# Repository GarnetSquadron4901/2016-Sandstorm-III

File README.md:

#2016 Robot Code - Sandstorm III - FIRST Robotics Team 4901 - Garnet Squadron

## Languages
- Robot - LabVIEW
- Dashboard - LabVIEW
- Vision Processing on Raspberry Pi
	- LED Control - Python
	- Vision Processing - Java using GRIP

## Features
- 8 drive modes
	- Arcade
	- Split Axis Arcade
	- Tank
	- Vision
	- Encoder Distance
	- Braked
	- Ultrasonic Distance
	- IMU Yaw Feedback
- Arm Control
	- PID
	- Preset Buttons
	- Manual arm control with closed-loop feedback from potentiometer
	- Automatic locking/unlocking with pneumatic cylinders
	- Automatic arm raising when driving faster than a preset speed
- Parameters - Most robot constants are parameterized to allow run-time changes to parameters such as arm angles, voltage to angle conversion, etc. 
- [Custom operator interface](https://github.com/GarnetSquardon4901/Operator-Interface-Control-Board)

## Checkout Process
To check out the Sandstorm III repository, simply download the [update.bat](https://github.com/GarnetSquardon4901/2016-Sand-Storm-III/raw/master/update.bat) and run it.

You'll need to install TortoiseSVN v1.8.x from [SourceForge](https://sourceforge.net/projects/tortoisesvn/files/). Newer versions (such as v1.9) don't work with the LabVIEW Plugin TSVN. Be sure to install the option for Command line tools.

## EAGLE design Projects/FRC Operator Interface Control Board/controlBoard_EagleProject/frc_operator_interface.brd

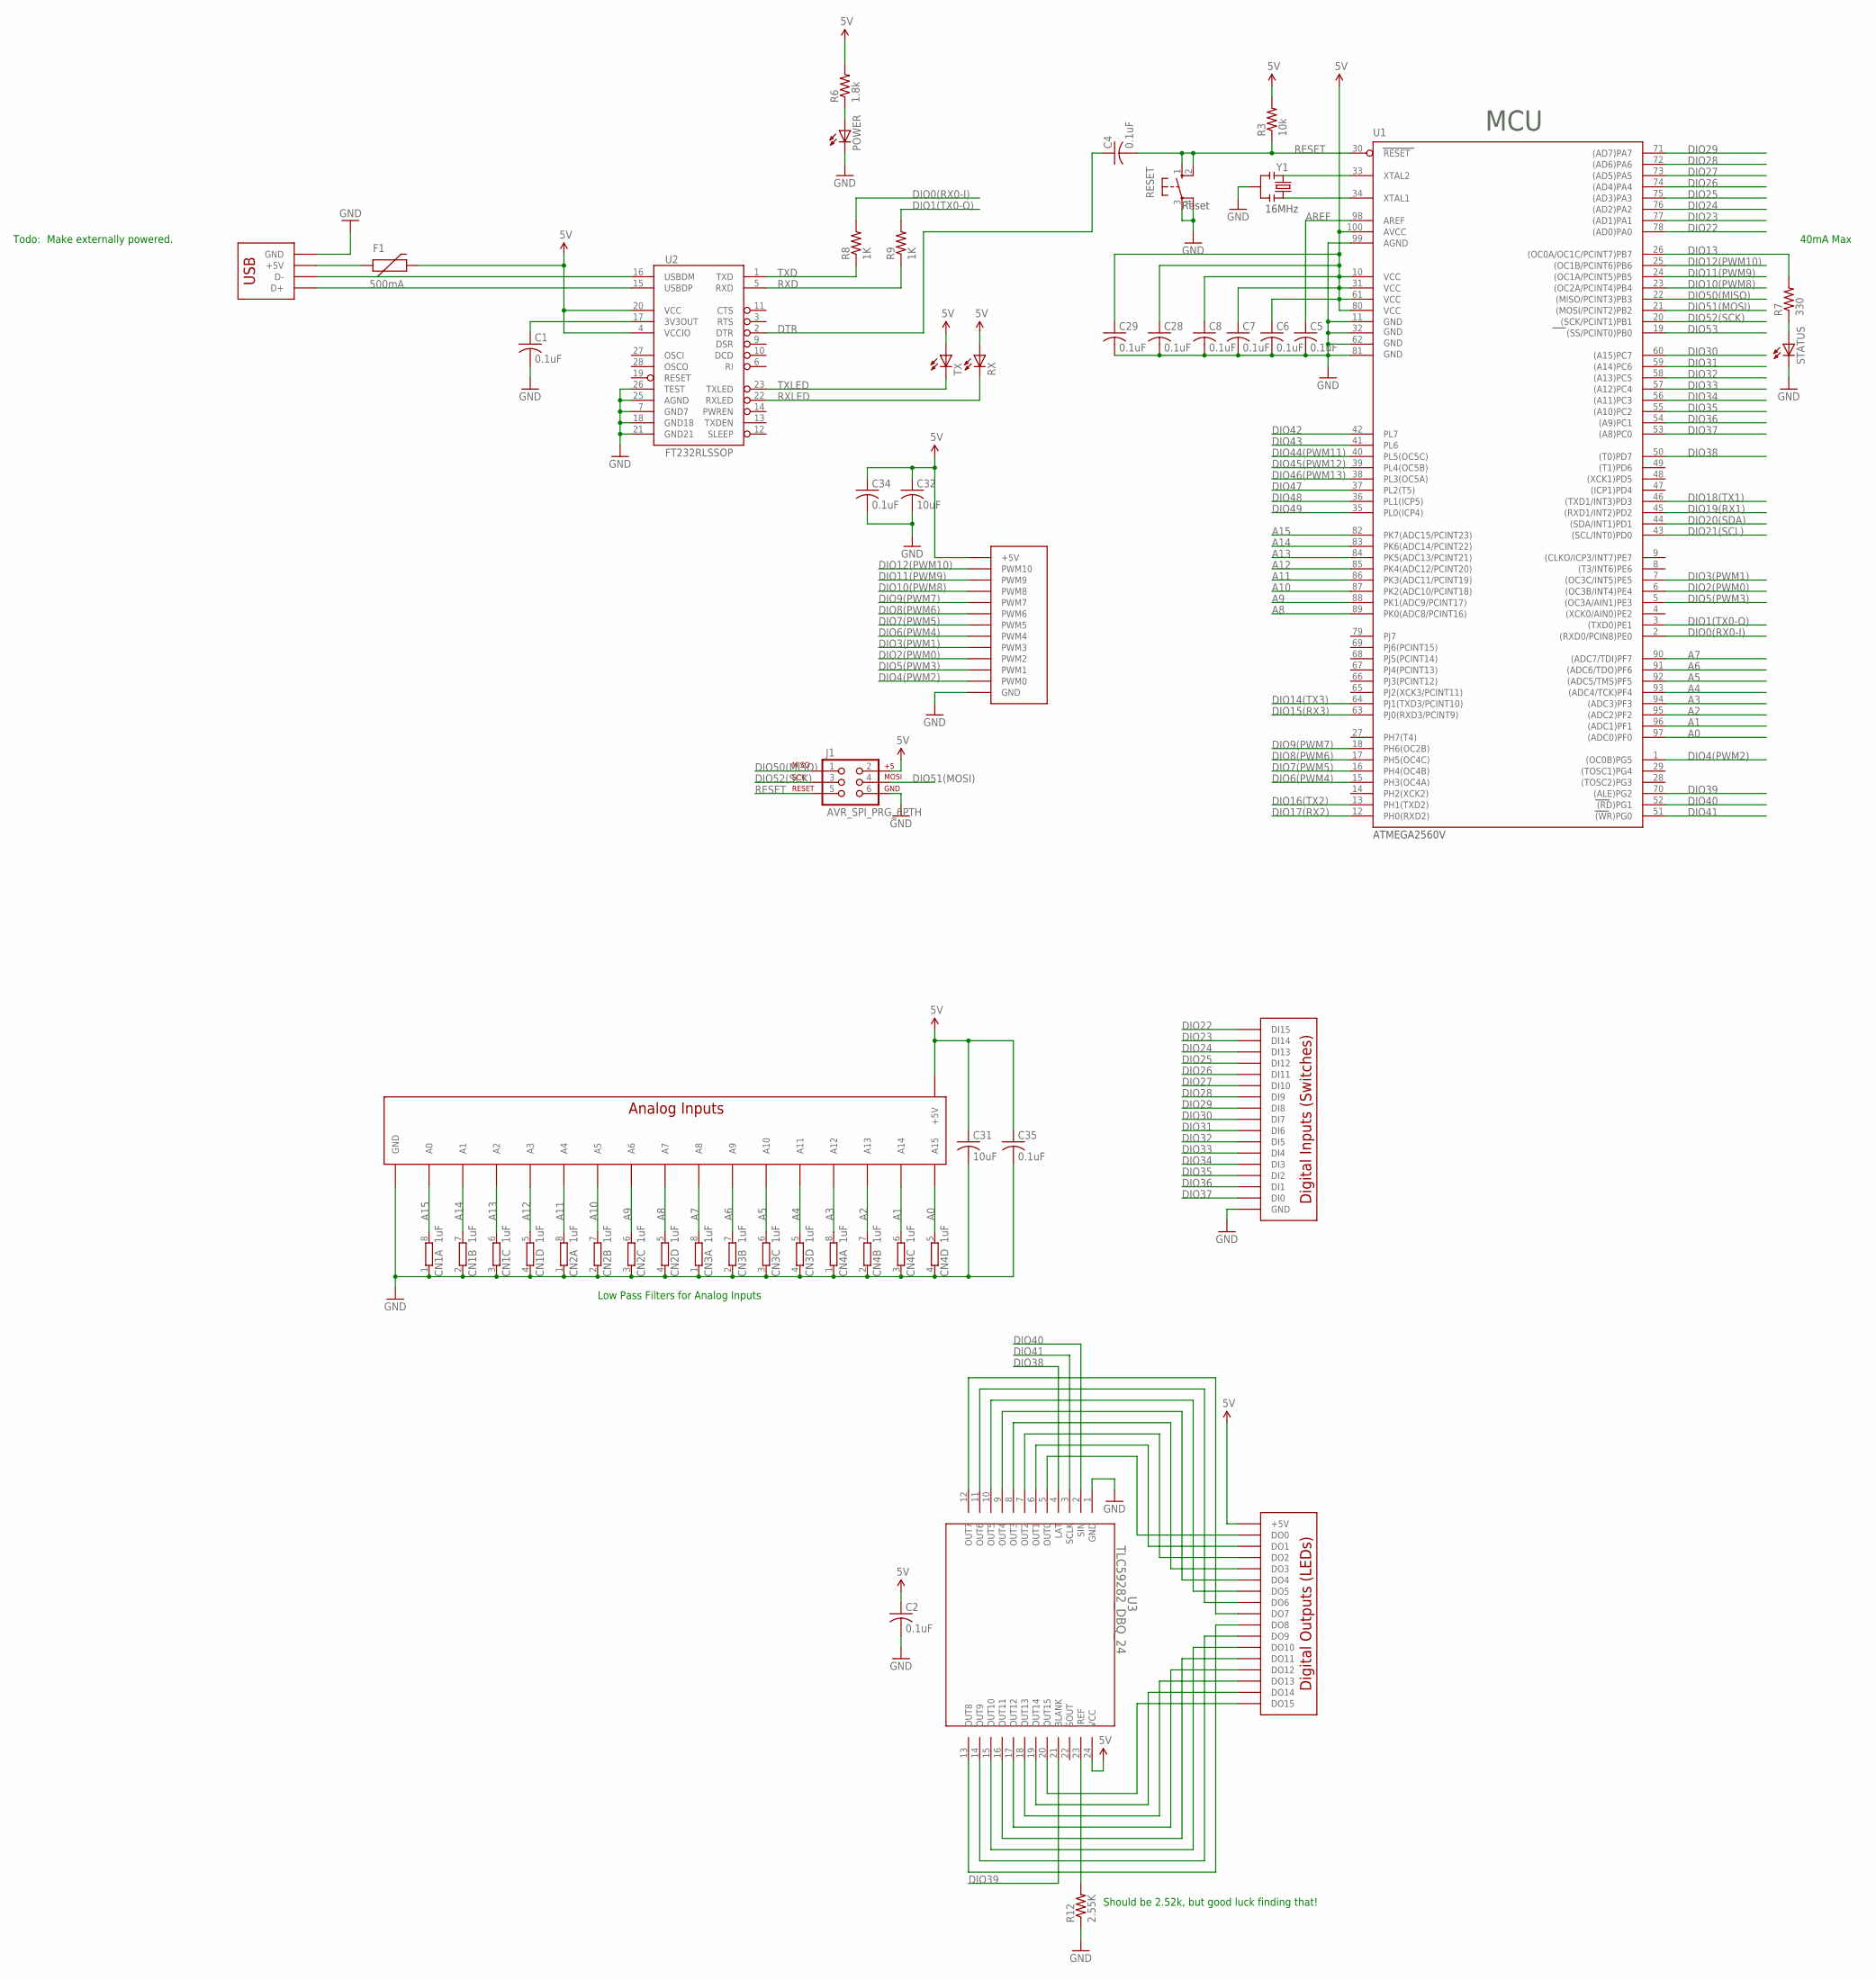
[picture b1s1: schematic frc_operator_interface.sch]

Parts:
C1, C2, C4, C5, C6, C7, C8, C28, C29, C34, C35: 0.1uF; C1206
C31, C32: 10uF; C1206
CN1, CN2, CN3, CN4: 1uF; EXB38V
F1: 500mA; PTC-1206
J1: AVR_SPI_PRG_6PTH; 2X3
J2: ANALOGHEADER
J3: DIGITALIN
J4: DIGITALOUTPUTS; DIGITALOUT
J5: PWMHEADER
J6: UE27BC54130-USB
POWER: LED3MM
R3: 10k; M1206
R6: 1.8k; M1206
R7: 330; M1206
R8, R9: 1K; M1206
R12: 2.55K; M1206
RESET: 10-XX; B3F-10XX
RX: LED3MM
STATUS: LED3MM
TX: LED3MM
U1: ATMEGA2560AU; TQFP100
U2: FT232RLSSOP; SSOP28DB
U3: TLC59282_DBQ_24; DBQ24
Y1: RESONATORSMD; RESONATOR-SMD

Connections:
5V: C2.1, C6.1, C7.1, C8.1, C28.1, C29.1, C31.1, C32.1, C34.1, C35.1, F1.2, J1.2, J2.+5V@0 (+5V), J2.+5V@1 (+5V), J2.+5V@2 (+5V), J2.+5V@3 (+5V), J2.+5V@4 (+5V), J2.+5V@5 (+5V), J2.+5V@6 (+5V), J2.+5V@7 (+5V), J2.+5V@8 (+5V), J2.+5V@9 (+5V), J2.+5V@10 (+5V), J2.+5V@11 (+5V), J2.+5V@12 (+5V), J2.+5V@13 (+5V), J2.+5V@14 (+5V), J2.+5V@15 (+5V), J4.+5V@0 (+5V), J4.+5V@1 (+5V), J4.+5V@2 (+5V), J4.+5V@3 (+5V), J4.+5V@4 (+5V), J4.+5V@5 (+5V), J4.+5V@6 (+5V), J4.+5V@7 (+5V), J4.+5V@8 (+5V), J4.+5V@9 (+5V), J4.+5V@10 (+5V), J4.+5V@11 (+5V), J4.+5V@12 (+5V), J4.+5V@13 (+5V), J4.+5V@14 (+5V), J4.+5V@15 (+5V), J5.+5V@3 (+5V), J5.+5V@4 (+5V), J5.+5V@5 (+5V), J5.+5V@6 (+5V), J5.+5V@7 (+5V), J5.+5V@8 (+5V), J5.+5V@9 (+5V), J5.+5V@10 (+5V), J5.+5V@11 (+5V), J5.+5V@12 (+5V), J5.+5V@13 (+5V), R3.2, R6.2, RX.A, TX.A, U1.10 (VCC), U1.31 (VCC1), U1.61 (VCC2), U1.80 (VCC3), U1.100 (AVCC), U2.4 (VCCIO), U2.20 (VCC), U3.24 (VCC)
A0: CN4.5 (2), J2.15 (A15), U1.97 ((ADC0)PF0)
A1: CN4.6 (2), J2.14 (A14), U1.96 ((ADC1)PF1)
A2: CN4.7 (2), J2.13 (A13), U1.95 ((ADC2)PF2)
A3: CN4.8 (2), J2.12 (A12), U1.94 ((ADC3)PF3)
A4: CN3.5 (2), J2.11 (A11), U1.93 ((ADC4/TCK)PF4)
A5: CN3.6 (2), J2.10 (A10), U1.92 ((ADC5/TMS)PF5)
A6: CN3.7 (2), J2.9 (A9), U1.91 ((ADC6/TDO)PF6)
A7: CN3.8 (2), J2.8 (A8), U1.90 ((ADC7/TDI)PF7)
A8: CN2.5 (2), J2.7 (A7), U1.89 (PK0(ADC8/PCINT16))
A9: CN2.6 (2), J2.6 (A6), U1.88 (PK1(ADC9/PCINT17))
A10: CN2.7 (2), J2.5 (A5), U1.87 (PK2(ADC10/PCINT18))
A11: CN2.8 (2), J2.4 (A4), U1.86 (PK3(ADC11/PCINT19))
A12: CN1.5 (2), J2.3 (A3), U1.85 (PK4(ADC12/PCINT20))
A13: CN1.6 (2), J2.2 (A2), U1.84 (PK5(ADC13/PCINT21))
A14: CN1.7 (2), J2.1 (A1), U1.83 (PK6(ADC14/PCINT22))
A15: CN1.8 (2), J2.0 (A0), U1.82 (PK7(ADC15/PCINT23))
AREF: C5.1, U1.98 (AREF)
DIO0(RX0-I): R8.2, U1.2 ((RXD0/PCIN8)PE0)
DIO1(TX0-O): R9.2, U1.3 ((TXD0)PE1)
DIO2(PWM0): J5.2 (PWM2), U1.6 ((OC3B/INT4)PE4)
DIO3(PWM1): J5.3 (PWM3), U1.7 ((OC3C/INT5)PE5)
DIO4(PWM2): J5.0 (PWM0), U1.1 ((OC0B)PG5)
DIO5(PWM3): J5.1 (PWM1), U1.5 ((OC3A/AIN1)PE3)
DIO6(PWM4): J5.4 (PWM4), U1.15 (PH3(OC4A))
DIO7(PWM5): J5.5 (PWM5), U1.16 (PH4(OC4B))
DIO8(PWM6): J5.6 (PWM6), U1.17 (PH5(OC4C))
DIO9(PWM7): J5.7 (PWM7), U1.18 (PH6(OC2B))
DIO10(PWM8): J5.8 (PWM8), U1.23 ((OC2A/PCINT4)PB4)
DIO11(PWM9): J5.9 (PWM9), U1.24 ((OC1A/PCINT5)PB5)
DIO12(PWM10): J5.10 (PWM10), U1.25 ((OC1B/PCINT6)PB6)
DIO13: R7.2, U1.26 ((OC0A/OC1C/PCINT7)PB7)
DIO14(TX3): U1.64 (PJ1(TXD3/PCINT10))
DIO15(RX3): U1.63 (PJ0(RXD3/PCINT9))
DIO16(TX2): U1.13 (PH1(TXD2))
DIO17(RX2): U1.12 (PH0(RXD2))
DIO18(TX1): U1.46 ((TXD1/INT3)PD3)
DIO19(RX1): U1.45 ((RXD1/INT2)PD2)
DIO20(SDA): U1.44 ((SDA/INT1)PD1)
DIO21(SCL): U1.43 ((SCL/INT0)PD0)
DIO22: J3.DI15, U1.78 ((AD0)PA0)
DIO23: J3.DI14, U1.77 ((AD1)PA1)
DIO24: J3.DI13, U1.76 ((AD2)PA2)
DIO25: J3.DI12, U1.75 ((AD3)PA3)
DIO26: J3.DI11, U1.74 ((AD4)PA4)
DIO27: J3.DI10, U1.73 ((AD5)PA5)
DIO28: J3.DI9, U1.72 ((AD6)PA6)
DIO29: J3.DI8, U1.71 ((AD7)PA7)
DIO30: J3.DI7, U1.60 ((A15)PC7)
DIO31: J3.DI6, U1.59 ((A14)PC6)
DIO32: J3.DI5, U1.58 ((A13)PC5)
DIO33: J3.DI4, U1.57 ((A12)PC4)
DIO34: J3.DI3, U1.56 ((A11)PC3)
DIO35: J3.DI2, U1.55 ((A10)PC2)
DIO36: J3.DI1, U1.54 ((A9)PC1)
DIO37: J3.DI0, U1.53 ((A8)PC0)
DIO38: U1.50 ((T0)PD7), U3.4 (LAT)
DIO39: U1.70 ((ALE)PG2), U3.21 (BLANK)
DIO40: U1.52 ((RD)PG1), U3.2 (SIN)
DIO41: U1.51 ((WR)PG0), U3.3 (SCLK)
DIO42: U1.42 (PL7)
DIO43: U1.41 (PL6)
DIO44(PWM11): U1.40 (PL5(OC5C))
DIO45(PWM12): U1.39 (PL4(OC5B))
DIO46(PWM13): U1.38 (PL3(OC5A))
DIO47: U1.37 (PL2(T5))
DIO48: U1.36 (PL1(ICP5))
DIO49: U1.35 (PL0(ICP4))
DIO50(MISO): J1.1, U1.22 ((MISO/PCINT3)PB3)
DIO51(MOSI): J1.4, U1.21 ((MOSI/PCINT2)PB2)
DIO52(SCK): J1.3, U1.20 ((SCK/PCINT1)PB1)
DIO53: U1.19 ((SS/PCINT0)PB0)
DTR: C4.1, U2.2 (DTR)
GND: C1.2, C2.2, C5.2, C6.2, C7.2, C8.2, C28.2, C29.2, C31.2, C32.2, C34.2, C35.2, CN1.1, CN1.2 (1), CN1.3 (1), CN1.4 (1), CN2.1, CN2.2 (1), CN2.3 (1), CN2.4 (1), CN3.1, CN3.2 (1), CN3.3 (1), CN3.4 (1), CN4.1, CN4.2 (1), CN4.3 (1), CN4.4 (1), J1.6, J2.GND@0 (GND), J2.GND@1 (GND), J2.GND@2 (GND), J2.GND@3 (GND), J2.GND@4 (GND), J2.GND@5 (GND), J2.GND@6 (GND), J2.GND@7 (GND), J2.GND@8 (GND), J2.GND@9 (GND), J2.GND@10 (GND), J2.GND@11 (GND), J2.GND@12 (GND), J2.GND@13 (GND), J2.GND@14 (GND), J2.GND@15 (GND), J3.GND@0 (GND), J3.GND@1 (GND), J3.GND@2 (GND), J3.GND@3 (GND), J3.GND@4 (GND), J3.GND@5 (GND), J3.GND@6 (GND), J3.GND@7 (GND), J3.GND@8 (GND), J3.GND@9 (GND), J3.GND@10 (GND), J3.GND@11 (GND), J3.GND@12 (GND), J3.GND@13 (GND), J3.GND@14 (GND), J3.GND@15 (GND), J5.GND@3 (GND), J5.GND@4 (GND), J5.GND@5 (GND), J5.GND@6 (GND), J5.GND@7 (GND), J5.GND@8 (GND), J5.GND@9 (GND), J5.GND@10 (GND), J5.GND@11 (GND), J5.GND@12 (GND), J5.GND@13 (GND), J6.GND@0 (GND), J6.GND@1 (GND), J6.GND@2 (GND), POWER.K (C), R12.1, RESET.3, RESET.4 (P1), STATUS.K (C), U1.11 (GND), U1.32 (GND1), U1.62 (GND2), U1.81 (GND3), U1.99 (AGND), U2.7 (GND7), U2.18 (GND18), U2.21 (GND21), U2.25 (AGND), U2.26 (TEST), U3.1 (GND), Y1.2
unnamed: POWER.A, R6.1
unnamed: R7.1, STATUS.A
unnamed: F1.1, J6.+5V
unnamed: C1.1, U2.17 (3V3OUT)
unnamed: J4.DO1, U3.6 (OUT1)
unnamed: J4.DO2, U3.7 (OUT2)
unnamed: J4.DO0, U3.5 (OUT0)
unnamed: J4.DO3, U3.8 (OUT3)
unnamed: J4.DO4, U3.9 (OUT4)
unnamed: J4.DO5, U3.10 (OUT5)
unnamed: J4.DO6, U3.11 (OUT6)
unnamed: J4.DO7, U3.12 (OUT7)
unnamed: J4.DO15, U3.20 (OUT15)
unnamed: J4.DO14, U3.19 (OUT14)
unnamed: J4.DO13, U3.18 (OUT13)
unnamed: J4.DO12, U3.17 (OUT12)
unnamed: J4.DO11, U3.16 (OUT11)
unnamed: J4.DO10, U3.15 (OUT10)
unnamed: J4.DO9, U3.14 (OUT9)
unnamed: J4.DO8, U3.13 (OUT8)
unnamed: R12.2, U3.23 (IREF)
unnamed: U1.33 (XTAL2), Y1.1
unnamed: U1.34 (XTAL1), Y1.3
RESET: C4.2, J1.5, R3.1, RESET.1 (S), RESET.2 (S1), U1.30 (RESET)
RXD: R9.1, U2.5 (RXD)
RXLED: RX.K (C), U2.22 (RXLED)
TXD: R8.1, U2.1 (TXD)
TXLED: TX.K (C), U2.23 (TXLED)
USB_D_N: J6.-DATA (D-), U2.16 (USBDM)
USB_D_P: J6.+DATA (D+), U2.15 (USBDP)

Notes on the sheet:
MCU
16MHz
ATMEGA2560V
Reset
Low Pass Filters for Analog Inputs
40mA Max
Todo:
Make externally powered.
Should be 2.52k, but good luck finding that!

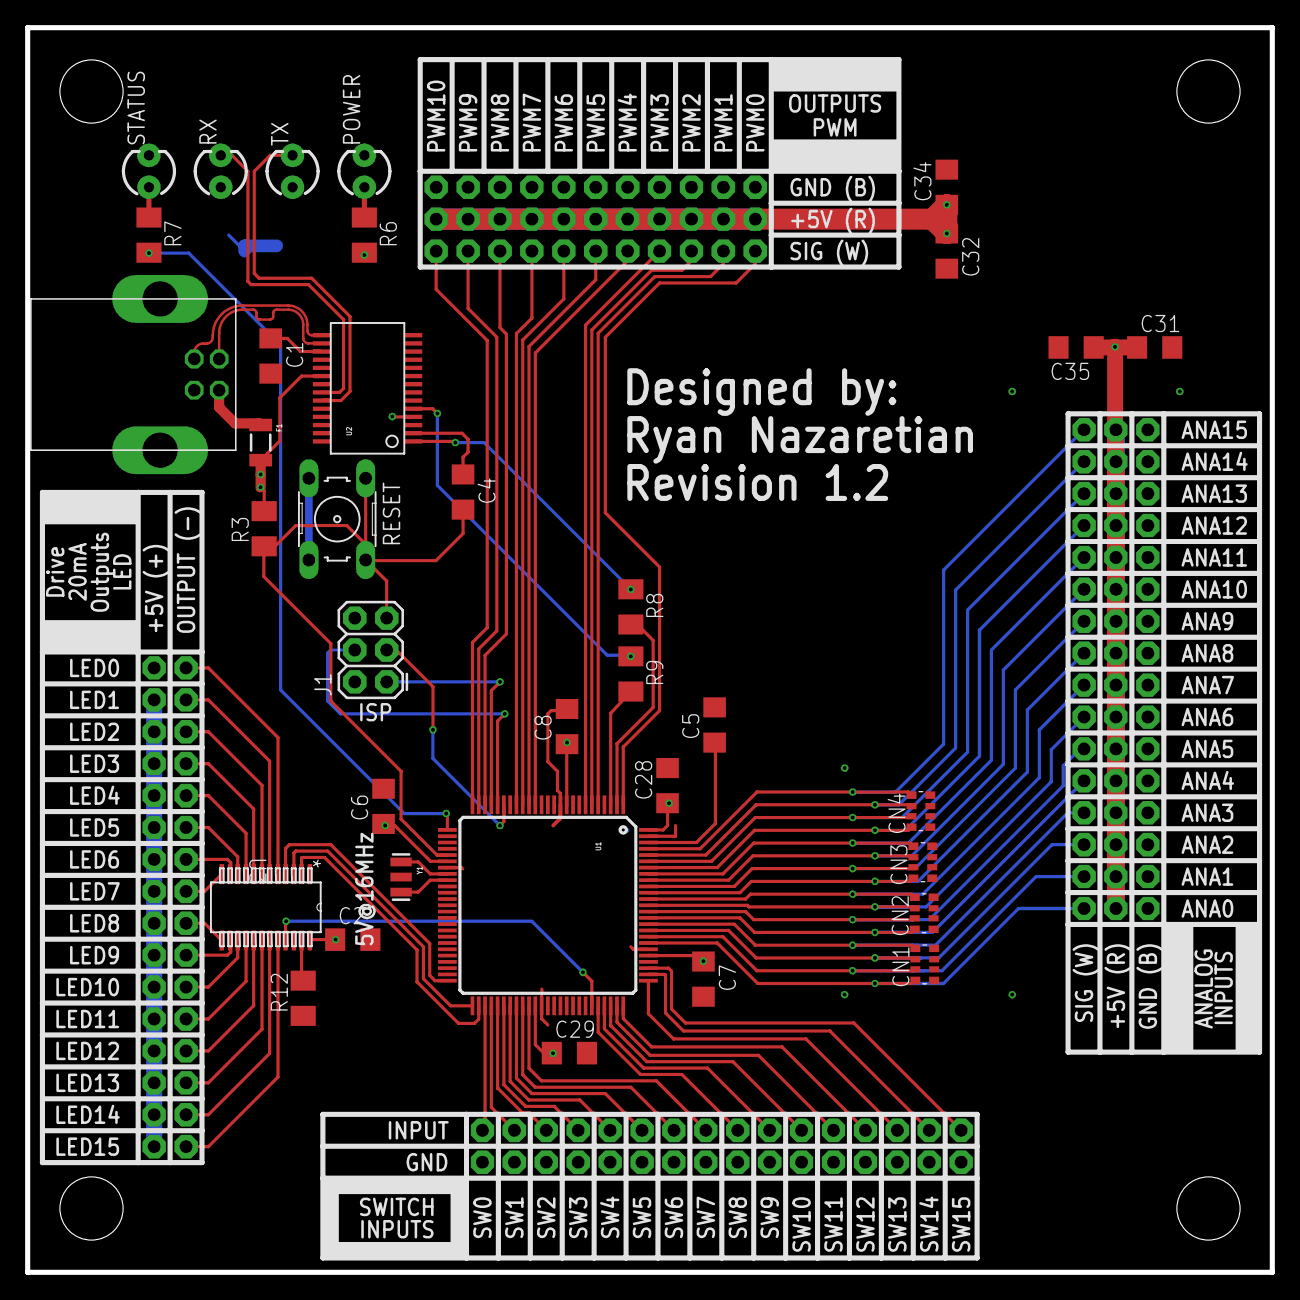
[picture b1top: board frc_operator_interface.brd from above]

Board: 2 copper layers, 99.1 x 99.1 mm, 39 parts (0 on the bottom side), 87 nets.

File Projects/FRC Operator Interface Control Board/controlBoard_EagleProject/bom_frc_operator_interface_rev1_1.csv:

Qty,Value,Device,Package,Parts,Description,DATASHEETURL,DESCRIPTION,FAMILY_NAME,DIGIKEY_PART_NUMBER,INDUSTRY_STD_PKG_TYPE,MANUFACTURER,MANUFACTURER_PART_NUMBER,MF,MPN,OC_FARNELL,OC_NEWARK,PACKAGE_DESIGNATOR,PIN_COUNT,PROD_ID,VENDOR
1,,10-XX,B3F-10XX,RESET,OMRON SWITCH,,Reset Switch,,SW400-ND,,,,,B3F-1000,176432,36M3542,,,,
4,,LED3MM,LED3MM,"POWER, RX, STATUS, TX",LEDs,,,,,,,,,,,,,,,
11,0.1uF,C-USC1206,C1206,"C1, C2, C4, C5, C6, C7, C8, C28, C29, C34, C35","CAPACITOR, American symbol",,,,,,,,,,,,,,,
1,10k,R-US_M1206,M1206,R3,"RESISTOR, American symbol",,,,,,,,,,,,,,,
2,10uF,C-USC1206,C1206,"C31, C32","CAPACITOR, American symbol",,,,,,,,,,,,,,,
1,170,R-US_M1206,M1206,R6,"RESISTOR, American symbol",,,,,,,,,,,,,,,
2,1K,R-US_M1206,M1206,"R8, R9","RESISTOR, American symbol",,,,,,,,,,,,,,,
4,1uF,4R-NEXB38V,EXB38V,"CN1, CN2, CN3, CN4",Array Chip Resistor,,,,,,,,,,unknown,unknown,,,,
1,2.52K,R-US_M1206,M1206,R12,"RESISTOR, American symbol",,,,,,,,,,,,,,,
1,280,R-US_M1206,M1206,R1,"RESISTOR, American symbol",,,,,,,,,,,,,,,
1,300,R-US_M1206,M1206,R7,"RESISTOR, American symbol",,,,,,,,,,,,,,,
1,315,R-US_M1206,M1206,R2,"RESISTOR, American symbol",,,,,,,,,,,,,,,
1,500mA,PTCSMD,PTC-1206,F1,Resettable Fuse PTC,,,,,,,,,,,,,,RES-11150,
1,ANALOGHEADER,ANALOGHEADER,ANALOGHEADER,U$12,,,,,,,,,,,,,,,,
1,ATMEGA2560AU,ATMEGA2560AU,TQFP100,GND,MICROCONTROLLER,,,,,,,,,,,,,,,
1,AVR_SPI_PRG_6PTH,AVR_SPI_PRG_6PTH,2X3,J1,AVR ISP 6 Pin,,,,,,,,,,,,,,,
1,DIGITALIN,DIGITALIN,DIGITALIN,U$2,,,,,,,,,,,,,,,,
1,DIGITALOUTPUTS,DIGITALOUTPUTS,DIGITALOUT,U$11,,,,,,,,,,,,,,,,
1,FT232RLSSOP,FT232RLSSOP,SSOP28DB,U4,USB UART,,,,,,,,,,,,,,,
1,PWMHEADER,PWMHEADER,PWMHEADER,U$10,,,,,,,,,,,,,,,,
1,RESONATORSMD,RESONATORSMD,RESONATOR-SMD,Y1,Resonator,,,,,,,,,,,,,,,
1,TLC59282_DBQ_24,TLC59282_DBQ_24,DBQ24,U1,,http://www.ti.com/lit/gpn/TLC59282,16-Channel Constant Current LED Driver with 4-Channel Grouped Delay,LED DRIVER,TLC59282,SSOP/QSOP,Texas Instruments,tlc59282_dbq_24,,,,,DBQ,24,,Texas Instruments
1,UE27BC54130-USB,UE27BC54130-USB,UE27BC54130-USB,U$14,,,,,,,,,,,,,,,,

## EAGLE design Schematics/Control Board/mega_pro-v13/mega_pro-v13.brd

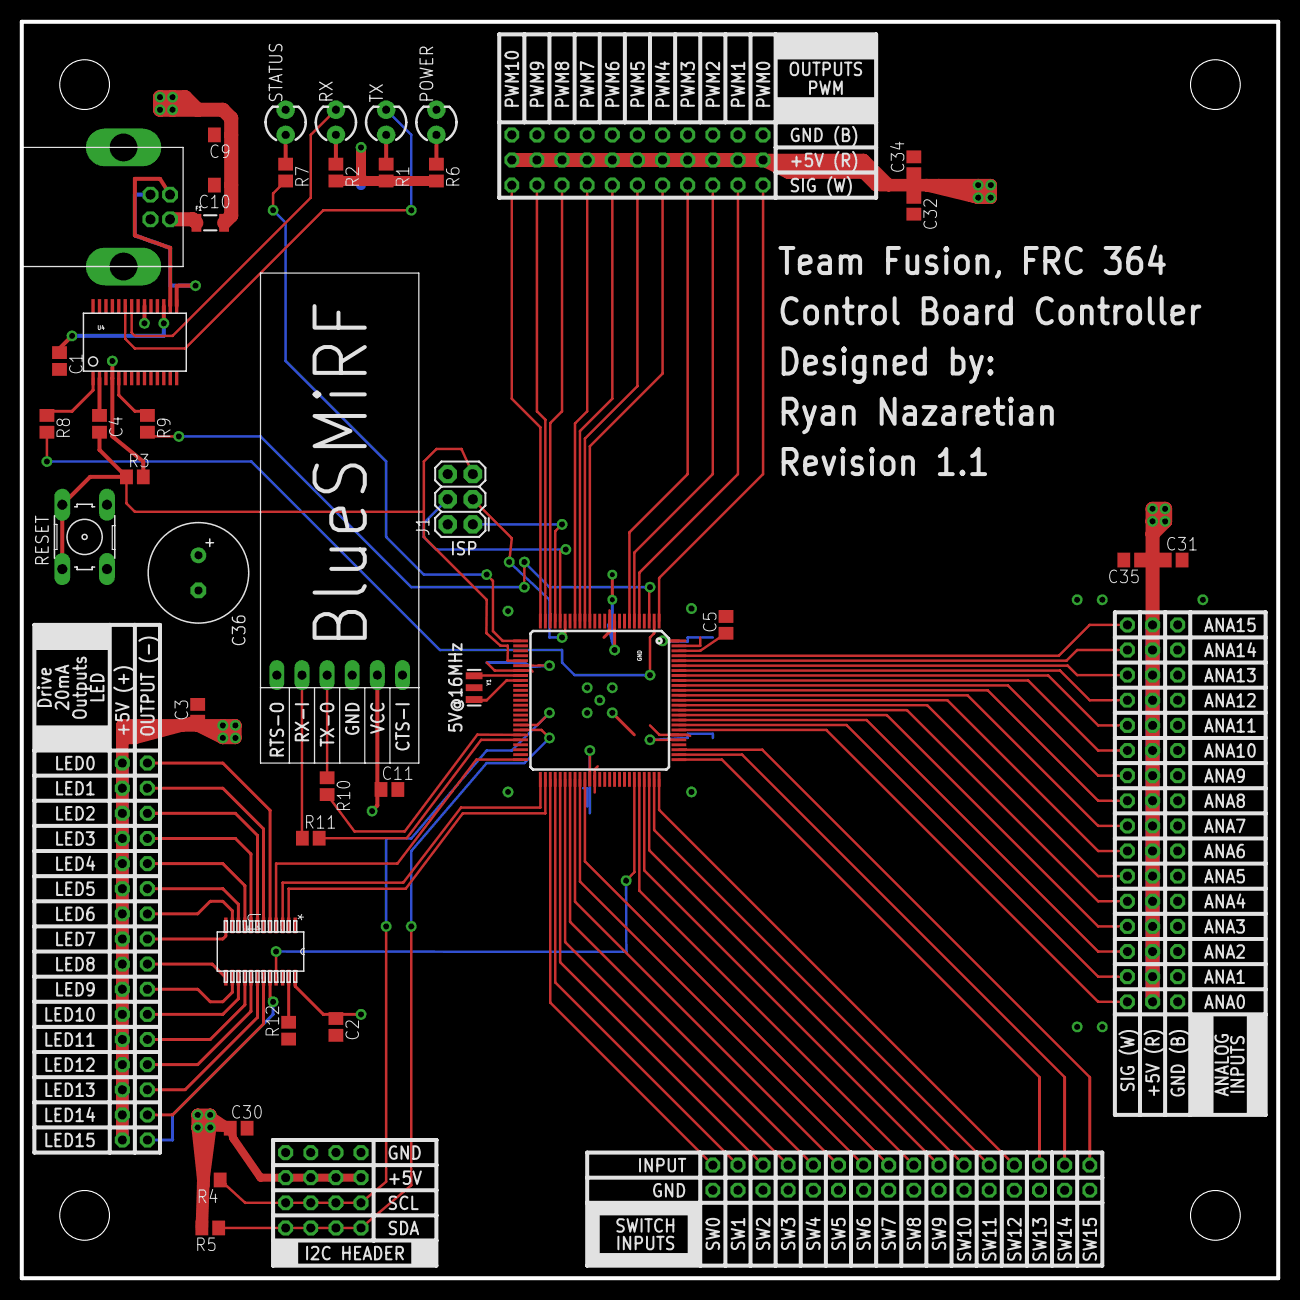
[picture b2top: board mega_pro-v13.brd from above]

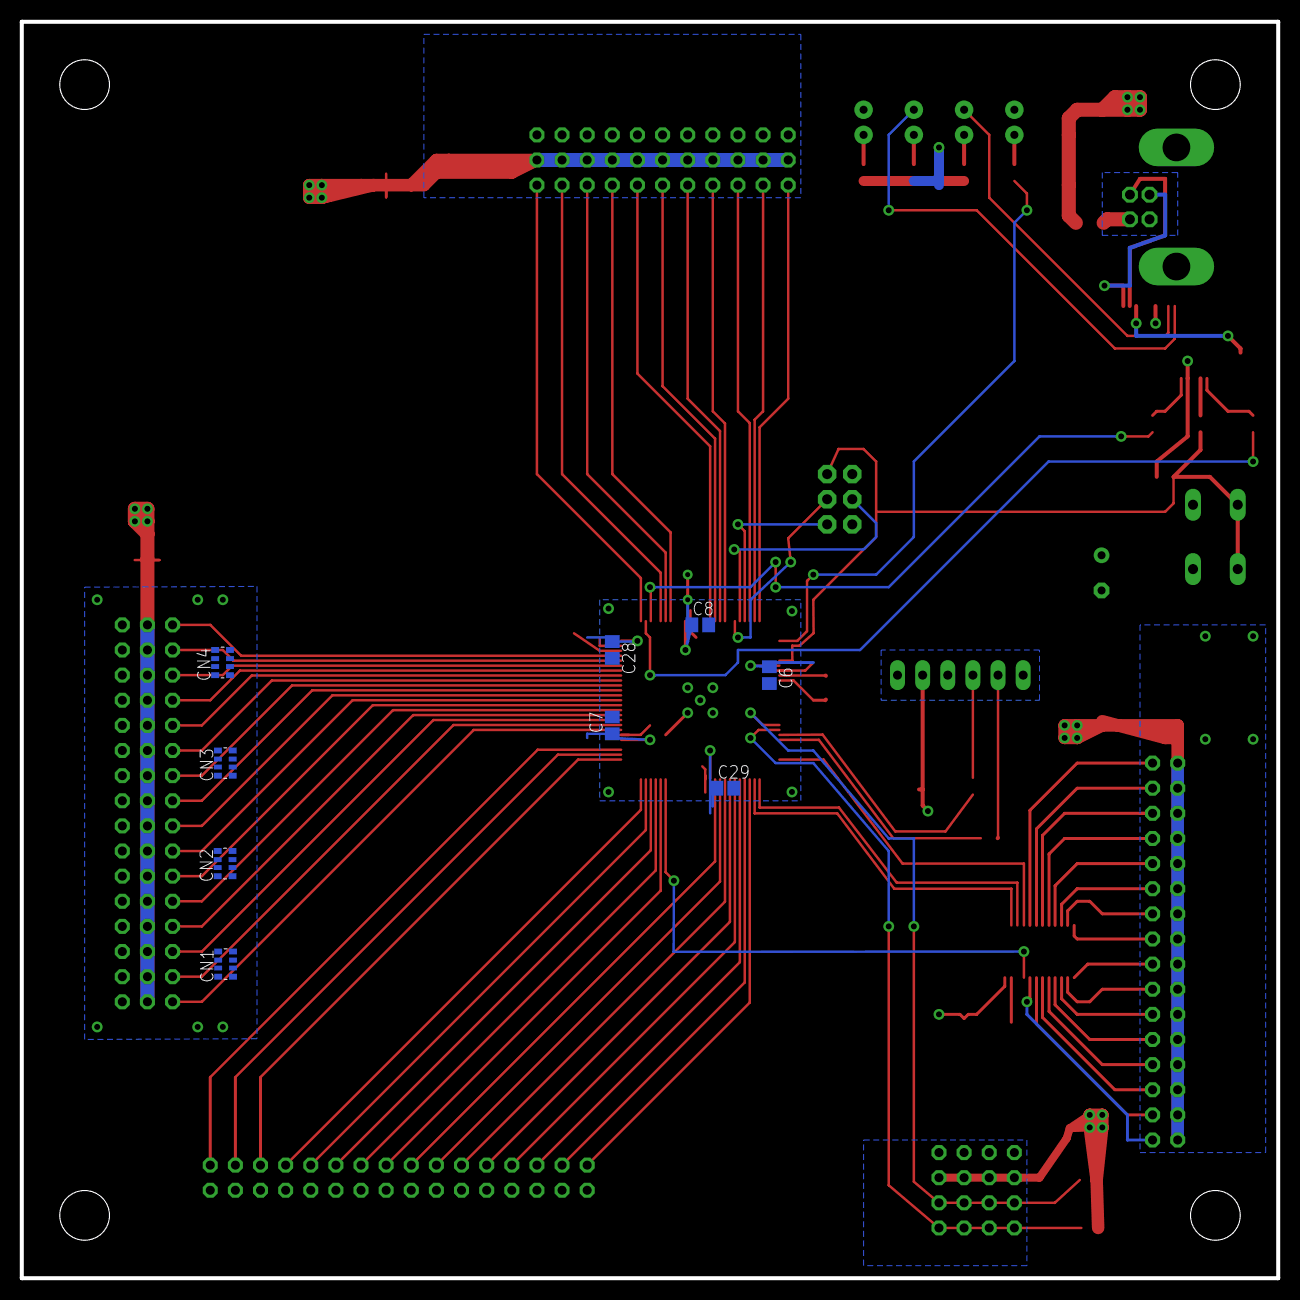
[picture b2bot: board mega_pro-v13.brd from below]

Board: 2 copper layers, 127.0 x 127.0 mm, 53 parts (9 on the bottom side), 95 nets.

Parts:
C1, C2, C4, C5, C6, C7, C8, C9, C28, C29, C34, C35: 0.1uF; C0805
C3, C10, C11, C30, C31, C32: 10uF; C0805
C36: 470uF; E3,5-10
CN1, CN2, CN3, CN4: 1uF; EXB38V
F1: 500mA; PTC-1206
GND: ATMEGA2560AU; TQFP100
J1: AVR_SPI_PRG_6PTH; 2X3
POWER: LED3MM
R1: 140; R0805
R2: 157.5; R0805
R3, R4, R5: 10k; R0805
R6: 85; R0805
R7: 150; R0805
R8, R9, R10, R11: 1K; R0805
R12: 2.52K; R0805
RESET: B3F-10XX
RX: LED3MM
STATUS: LED3MM
TX: LED3MM
U1: TLC59282_DBQ_24; DBQ24
U4: FT232RLSSOP; SSOP28DB
U$2: DIGITALIN
U$10: PWMHEADER
U$11: DIGITALOUTPUTS; DIGITALOUT
U$12: ANALOGHEADER
U$14: UE27BC54130-USB
U$15: I2CHEADER
U$19: BLUESMIRF
Y1: RESONATORSMD; RESONATOR-SMD

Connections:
5V: C2.1, C3.1, C6.1, C7.1, C8.1, C9.1, C10.1, C11.1, C28.1, C29.1, C30.1, C31.1, C32.1, C34.1, C35.1, C36.+, F1.2, GND.10, GND.31, GND.61, GND.80, GND.100, J1.2, R1.2, R2.2, R3.2, R4.2, R5.2, R6.2, U1.24, U4.4, U4.20, U$10.+5V@3, U$10.+5V@4, U$10.+5V@5, U$10.+5V@6, U$10.+5V@7, U$10.+5V@8, U$10.+5V@9, U$10.+5V@10, U$10.+5V@11, U$10.+5V@12, U$10.+5V@13, U$11.+5V@0, U$11.+5V@1, U$11.+5V@2, U$11.+5V@3, U$11.+5V@4, U$11.+5V@5, U$11.+5V@6, U$11.+5V@7, U$11.+5V@8, U$11.+5V@9, U$11.+5V@10, U$11.+5V@11, U$11.+5V@12, U$11.+5V@13, U$11.+5V@14, U$11.+5V@15, U$12.+5V@0, U$12.+5V@1, U$12.+5V@2, U$12.+5V@3, U$12.+5V@4, U$12.+5V@5, U$12.+5V@6, U$12.+5V@7, U$12.+5V@8, U$12.+5V@9, U$12.+5V@10, U$12.+5V@11, U$12.+5V@12, U$12.+5V@13, U$12.+5V@14, U$12.+5V@15, U$15.VCC@0, U$15.VCC@1, U$15.VCC@2, U$15.VCC@3, U$19.VCC
A0: CN4.5, GND.97, U$12.15
A1: CN4.6, GND.96, U$12.14
A2: CN4.7, GND.95, U$12.13
A3: CN4.8, GND.94, U$12.12
A4: CN3.5, GND.93, U$12.11
A5: CN3.6, GND.92, U$12.10
A6: CN3.7, GND.91, U$12.9
A7: CN3.8, GND.90, U$12.8
A8: CN2.5, GND.89, U$12.7
A9: CN2.6, GND.88, U$12.6
A10: CN2.7, GND.87, U$12.5
A11: CN2.8, GND.86, U$12.4
A12: CN1.5, GND.85, U$12.3
A13: CN1.6, GND.84, U$12.2
A14: CN1.7, GND.83, U$12.1
A15: CN1.8, GND.82, U$12.0
AREF: C5.1, GND.98
DIO0(RX0-I): GND.2, R8.2
DIO1(TX0-O): GND.3, R9.2
DIO2(PWM0): GND.6, U$10.2
DIO3(PWM1): GND.7, U$10.3
DIO4(PWM2): GND.1, U$10.0
DIO5(PWM3): GND.5, U$10.1
DIO6(PWM4): GND.15, U$10.4
DIO7(PWM5): GND.16, U$10.5
DIO8(PWM6): GND.17, U$10.6
DIO9(PWM7): GND.18, U$10.7
DIO10(PWM8): GND.23, U$10.8
DIO11(PWM9): GND.24, U$10.9
DIO12(PWM10): GND.25, U$10.10
DIO13: GND.26, R7.2
DIO18(TX1): GND.46, R11.2
DIO19(RX1): GND.45, R10.2
DIO20(SDA): GND.44, R5.1, U$15.SDA@0, U$15.SDA@1, U$15.SDA@2, U$15.SDA@3
DIO21(SCL): GND.43, R4.1, U$15.SCL@0, U$15.SCL@1, U$15.SCL@2, U$15.SCL@3
DIO22: GND.78, U$2.DI15
DIO23: GND.77, U$2.DI14
DIO24: GND.76, U$2.DI13
DIO25: GND.75, U$2.DI12
DIO26: GND.74, U$2.DI11
DIO27: GND.73, U$2.DI10
DIO28: GND.72, U$2.DI9
DIO29: GND.71, U$2.DI8
DIO30: GND.60, U$2.DI7
DIO31: GND.59, U$2.DI6
DIO32: GND.58, U$2.DI5
DIO33: GND.57, U$2.DI4
DIO34: GND.56, U$2.DI3
DIO35: GND.55, U$2.DI2
DIO36: GND.54, U$2.DI1
DIO37: GND.53, U$2.DI0
DIO38: GND.50, U1.4
DIO39: GND.70, U1.21
DIO40: GND.52, U1.2
DIO41: GND.51, U1.3
DIO50(MISO): GND.22, J1.1
DIO51(MOSI): GND.21, J1.4
DIO52(SCK): GND.20, J1.3
DTR: C4.1, U4.2
GND: C1.2, C2.2, C3.2, C5.2, C6.2, C7.2, C8.2, C9.2, C10.2, C11.2, C28.2, C29.2, C30.2, C31.2, C32.2, C34.2, C35.2, C36.-, CN1.1, CN1.2, CN1.3, CN1.4, CN2.1, CN2.2, CN2.3, CN2.4, CN3.1, CN3.2, CN3.3, CN3.4, CN4.1, CN4.2, CN4.3, CN4.4, GND.11, GND.32, GND.62, GND.81, GND.99, J1.6, POWER.K, R12.1, RESET.3, RESET.4, STATUS.K, U1.1, U4.7, U4.18, U4.21, U4.25, U4.26, U$2.GND@0, U$2.GND@1, U$2.GND@2, U$2.GND@3, U$2.GND@4, U$2.GND@5, U$2.GND@6, U$2.GND@7, U$2.GND@8, U$2.GND@9, U$2.GND@10, U$2.GND@11, U$2.GND@12, U$2.GND@13, U$2.GND@14, U$2.GND@15, U$10.GND@3, U$10.GND@4, U$10.GND@5, U$10.GND@6, U$10.GND@7, U$10.GND@8, U$10.GND@9, U$10.GND@10, U$10.GND@11, U$10.GND@12, U$10.GND@13, U$12.GND@0, U$12.GND@1, U$12.GND@2, U$12.GND@3, U$12.GND@4, U$12.GND@5, U$12.GND@6, U$12.GND@7, U$12.GND@8, U$12.GND@9, U$12.GND@10, U$12.GND@11, U$12.GND@12, U$12.GND@13, U$12.GND@14, U$12.GND@15, U$14.GND@0, U$14.GND@1, U$14.GND@2, U$15.GND@0, U$15.GND@1, U$15.GND@2, U$15.GND@3, U$19.GND, Y1.2
unnamed: R1.1, TX.A
unnamed: POWER.A, R6.1
unnamed: R7.1, STATUS.A
unnamed: F1.1, U$14.+5V
unnamed: R2.1, RX.A
unnamed: R10.1, U$19.TX-O
unnamed: R11.1, U$19.RX-I
unnamed: C1.1, U4.17
unnamed: U1.6, U$11.DO1
unnamed: U1.7, U$11.DO2
unnamed: U1.5, U$11.DO0
unnamed: U1.8, U$11.DO3
unnamed: U1.9, U$11.DO4
unnamed: U1.10, U$11.DO5
unnamed: U1.11, U$11.DO6
unnamed: U1.12, U$11.DO7
unnamed: U1.20, U$11.DO15
unnamed: U1.19, U$11.DO14
unnamed: U1.18, U$11.DO13
unnamed: U1.17, U$11.DO12
unnamed: U1.16, U$11.DO11
unnamed: U1.15, U$11.DO10
unnamed: U1.14, U$11.DO9
unnamed: U1.13, U$11.DO8
unnamed: R12.2, U1.23
unnamed: GND.33, Y1.1
unnamed: GND.34, Y1.3
RESET: C4.2, GND.30, J1.5, R3.1, RESET.1, RESET.2
RXD: R9.1, U4.5
RXLED: RX.K, U4.22
TXD: R8.1, U4.1
TXLED: TX.K, U4.23
USB_D+: U4.15, U$14.+DATA
USB_D-: U4.16, U$14.-DATA

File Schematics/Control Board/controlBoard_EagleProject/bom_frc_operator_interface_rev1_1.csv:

Qty,Value,Device,Package,Parts,Description,DATASHEETURL,DESCRIPTION,FAMILY_NAME,GENERIC_PART_NUMBER,INDUSTRY_STD_PKG_TYPE,MANUFACTURER,MANUFACTURER_PART_NUMBER,MF,MPN,OC_FARNELL,OC_NEWARK,PACKAGE_DESIGNATOR,PIN_COUNT,PROD_ID,VENDOR
1,,10-XX,B3F-10XX,RESET,OMRON SWITCH,,,,,,,,,B3F-1000,176432,36M3542,,,,
4,,LED3MM,LED3MM,"POWER, RX, STATUS, TX",LEDs,,,,,,,,,,,,,,,
11,0.1uF,C-USC1206,C1206,"C1, C2, C4, C5, C6, C7, C8, C28, C29, C34, C35","CAPACITOR, American symbol",,,,,,,,,,,,,,,
1,10k,R-US_M1206,M1206,R3,"RESISTOR, American symbol",,,,,,,,,,,,,,,
2,10uF,C-USC1206,C1206,"C31, C32","CAPACITOR, American symbol",,,,,,,,,,,,,,,
1,170,R-US_M1206,M1206,R6,"RESISTOR, American symbol",,,,,,,,,,,,,,,
2,1K,R-US_M1206,M1206,"R8, R9","RESISTOR, American symbol",,,,,,,,,,,,,,,
4,1uF,4R-NEXB38V,EXB38V,"CN1, CN2, CN3, CN4",Array Chip Resistor,,,,,,,,,,unknown,unknown,,,,
1,2.52K,R-US_M1206,M1206,R12,"RESISTOR, American symbol",,,,,,,,,,,,,,,
1,280,R-US_M1206,M1206,R1,"RESISTOR, American symbol",,,,,,,,,,,,,,,
1,300,R-US_M1206,M1206,R7,"RESISTOR, American symbol",,,,,,,,,,,,,,,
1,315,R-US_M1206,M1206,R2,"RESISTOR, American symbol",,,,,,,,,,,,,,,
1,500mA,PTCSMD,PTC-1206,F1,Resettable Fuse PTC,,,,,,,,,,,,,,RES-11150,
1,ANALOGHEADER,ANALOGHEADER,ANALOGHEADER,U$12,,,,,,,,,,,,,,,,
1,ATMEGA2560AU,ATMEGA2560AU,TQFP100,GND,MICROCONTROLLER,,,,,,,,,,,,,,,
1,AVR_SPI_PRG_6PTH,AVR_SPI_PRG_6PTH,2X3,J1,AVR ISP 6 Pin,,,,,,,,,,,,,,,
1,DIGITALIN,DIGITALIN,DIGITALIN,U$2,,,,,,,,,,,,,,,,
1,DIGITALOUTPUTS,DIGITALOUTPUTS,DIGITALOUT,U$11,,,,,,,,,,,,,,,,
1,FT232RLSSOP,FT232RLSSOP,SSOP28DB,U4,USB UART,,,,,,,,,,,,,,,
1,PWMHEADER,PWMHEADER,PWMHEADER,U$10,,,,,,,,,,,,,,,,
1,RESONATORSMD,RESONATORSMD,RESONATOR-SMD,Y1,Resonator,,,,,,,,,,,,,,,
1,TLC59282_DBQ_24,TLC59282_DBQ_24,DBQ24,U1,,http://www.ti.com/lit/gpn/TLC59282,16-Channel Constant Current LED Driver with 4-Channel Grouped Delay,LED DRIVER,TLC59282,SSOP/QSOP,Texas Instruments,tlc59282_dbq_24,,,,,DBQ,24,,Texas Instruments
1,UE27BC54130-USB,UE27BC54130-USB,UE27BC54130-USB,U$14,,,,,,,,,,,,,,,,

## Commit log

2015-11-09 Initial commit
    Initial commit. Worked on a sensor training presentation.
2015-11-11 Added control board documentation.
    Added the custom control board I designed along with the software
    libraries and firmware used with it.
2015-11-20 Corrected the pinout for the 2015 robot.
2015-11-21 Setup the robot to use joystick with arcade drive
2015-12-05 Finished 2015 Robot Code - Needs Testing
2015-12-23 Updated control board schematics and board layout
2015-12-24 Final control board revision 1.1
2015-12-24 Added BOM & cleaned up the control board project folder
2015-12-24 Removed 2016 project (we haven't started yet!), Added some Ri3d files to save myself a bit of time.
2015-12-24 Updated BOM for FRC OI Control Board
2016-01-01 Renamed the datasheet for the FTDI FT232R
2016-01-01 Add PCB top image for CD
2016-01-01 Added bottom image.
2016-01-01 Resized image
2016-01-01 Resized it again.
2016-01-01 Moved LabVIEW code for the control board to the control board project folder
2016-01-01 Renamed files, cleaned up demo
2016-01-06 Updated the sensors documentation.
2016-01-07 Removed temporary files, updated bill-of-material for control board, renamed some parts.
2016-01-07 Removed more temporary files
2016-01-07 Moved 2015 projects around a bit.
2016-01-07 Moved files around to support multiple sub-teams. Added RoboRIO documentation.
2016-01-08 Added REV Digit MXP Pre-release code from 1538
2016-01-08 Added recording autonomous code example
2016-01-08 Added Beta folder
2016-01-08 Added 2016 stuff, including the encrypted manual.
2016-01-09 Added game manual password
2016-01-10 Added initial Ri3d RoboRIO LabVIEW code to drive 4 motors. Documentation was updated in 2016 Ri3D\Electrical/2016 Ri3d RoboRIO Pinout.xlsx.
2016-01-10 Added Manipulator references. Cleaned up Begin.
2016-01-10 Updated project structure for new manipulator.
2016-01-10 Added some REV Robotics Support for LabVIEW NOTE: Some of the character map is messed up, probably due to a slight electrical change between the implementation from Adafruit, 1538, and REV Robotics.
2016-01-10 Moved REV Robotics files up a directory, added a demo screenshot.
2016-01-10 Updated character table. Not all are pretty, but they work.
2016-01-10 Added scrolling text.
2016-01-10 Fixed a few REV Digit bugs, added more functions such as write digit, write battery voltage.
2016-01-10 Added current display, and access to the buttons and adjustment potentiometer.
2016-01-10 Re-added battery voltage. Not sure why I deleted it. Thank goodness for version control! Added a deadband for the adjustment potentiometer.
2016-01-10 Tested shooter and beater bar functionality. Moving on to autonomous.
2016-01-11 Added compressor and solenoid to project.
2016-01-12 Ri3d - 3rd night push. Everything seems to work.
2016-01-12 Added arm code. Plug a Victor SP into PWM5. Use left joystick buttons 6 & 7 to control it.
2016-01-12 Changed arm speed from 100% to 33%.
2016-01-12 Fixed the pneumatic solenoid open problem.
2016-01-13 Added kickoff files
2016-01-14 Added unencrypted game manuals.
2016-01-14 Added template robot and dashboard code for the 2016 robot.
2016-01-14 Added John's CAD of the frame perimeter.
2016-01-14 Converted individual files to a LabVIEW VI Library
2016-01-15 Fixed various bugs after the library port.
2016-01-15 Update to 2016 robot code project. Begin the Neopixels on CAN project. Removed individual REV Digit files.
2016-01-15 Added Write Array function. Added screenshot demonstrations.
2016-01-18 Added Neopixel code.
2016-01-19 Changed joysticks to split-axis arcade. Updated Digit code to new library.
2016-01-19 Created robot drive code
2016-01-19 Hopefully fixed the character map for the last time. No idea why the map isn't saving. Added a tester / calibration program to try it locally on the computer.
2016-01-20 Fixed a bug in the Digit library.
2016-01-21 Cleaned up 2016 code a bit. Moved joystick code to a specific joystick folder. Added an overview document for the FRC Control Board
2016-01-24 Updated the resistor values for some of the LEDs on the board. Controller board code update commit.
2016-01-25 Working control board code.
2016-01-25 Fixed a bug with the shift-in for the switch read that offset the inputs by one.
2016-02-05 Added encoders to robot code.
2016-02-05 Moved documentation.
2016-02-06 Added GRIP vision processing. Moved 2015 game rules to 2015 folder. Added initial control board design.
2016-02-06 Added vision processing images.
2016-02-06 Added in all the hardware references to the robot code. Began work on the dashboard. Updated the robot pinout.
2016-02-08 Removed a bunch of stuff from the dashboard to make it easier to update.
2016-02-09 Monday commit. Dashboard image working.
2016-02-09 Commit of progress. Working on drive base control in Periodic Tasks.vi
2016-02-10 Progress from today. Continued drive base code in Periodic Tasks.vi
2016-02-11 Updated the 2016 schematic and autonomous ideas.
2016-02-12 Added special button controls for driver to change direction. Added controls for operator. Added arm control operated through the operator.
2016-02-13 Finished arm control code.
2016-02-13 Added 4 Drive CIM motors Added Access Point
2016-02-13 Worked on the drive base code.
2016-02-16 Fixed a conversion bug from decimal to string in the analog read section of code.
2016-02-16 Added control board model.
2016-02-16 Added team font.
2016-02-17 Added 4902 Inventor Full CAD
2016-02-17 Updated schematics, updated vision, added leds.
2016-02-18 Shooter working. Arm mode setting finished. Removed Network Variables from Control Board update loop.
2016-02-18 Big code push from today... Nothing tested, but I believe everything except autonomous is in here and should be somewhat functional. Some notes: - Parameterized most of the constants used in the prog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
2016-02-18 Robot parameter file.
2016-02-18 Some bug fixes from today's earlier's push.
2016-02-19 Added vision overlays to the dashboard.
2016-02-19 Updated the schematics a bit. Still work to do here.
2016-02-19 Fixed some bugs while recording the screenshot video.
2016-02-23 Calibrated arm sensor and fixed various bugs.
2016-02-24 Added half speed button to right joystick for more precise turning.
2016-02-24 Added drive base slew rate control. Added exception functionality for arm-autolock. Changed lock detection to unlock detection to prevent the arm from binding up. Fixed a bug with the arm momentarily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
2016-02-26 Added autonomous and made arm raise to cross defense level if the robot is going more than 1 ft/sec. Worked on dashboard.
2016-02-27 Friday commit. Dashboard autonomous reporting was fixed. Small tweaks for the robot.
2016-02-29 Updated the RPi start and mjpg streamer scripts.
2016-03-03 Made the variables pane fill up the screen area.
2016-03-04 Added some network table utilities.
2016-03-08 Changed robot parameters from using the XML to using Network Table variables which will use persistence.
2016-03-12 Thursday & Friday commit of Orlando.
2016-03-12 Added correct persistent.ini file for our robot parameters.
2016-03-14 Orlando Final
2016-03-16 Moved most of the files to their own repo for better version controlling. Left REV Robotics Digit code in until I get a confirmation that they switched their links.
2016-03-18 Removed REV Digit code, located on separate repo now. Readded all the robot code.
2016-03-18 Removed REV library.
2016-03-23 Linked the projects to the separate repositories.
2016-03-23 Added an update/setup utility for the Sand Storm III repository.
2016-03-23 Updated links with the OICB changes. Renamed project and updated the update.bat.
2016-03-25 Reduced the console clutter by turning Echo off.
2016-03-26 New GRIP file. I think the old one corrupted.
2016-04-27 Added files found on my flash drive.
2016-07-03 Started working on the Python code.
2016-07-03 Finished implemented. TODO: Add documentation.
2016-07-08 Python port progress commit.
2016-07-08 Updated VIs for new ADIS code.
2016-07-11 Finished Maxbotix code.
2016-07-11 Progress commit on Python porting.
2016-07-12 Finished Logitech Attack 3 class. Added joysticks to the mode_Init file.
2016-07-12 Added other files I've been working on that I haven't finished.
2016-07-18 Obviously not finished, but got tests to pass. Good milestone if something bad happens.
2016-07-22 Finished PID controller code.
2016-07-23 Worked on LabVIEW PID for the drive encoders. Trying to get Python code to work in Simulation and pass tests at the same time.
2016-07-23 Teleop drive motors working.
2016-07-23 Added better mode change message.
2016-08-21 Removed Python code from this repo since it was moved to its own repo.
2016-10-13 Removed limit switch function
2016-10-15 Switch dashboard to use the camera connected to the roboRIO. Removed air pressure gauge.
2016-10-17 Changed GitHub URL in update.bat.

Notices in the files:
parts and their libraries:
SparkFun-LED: Licensing: CC v3.0 Share-Alike You are welcome to use this library for commercial purposes.
